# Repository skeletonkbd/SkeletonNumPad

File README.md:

# SkeletonNumPad

シンプルなNumpadです。現在、販売開始の準備中。

## 特徴
- アクリル積層ケース
- バックライトLED
- ホットスワップ

# 組み立て例

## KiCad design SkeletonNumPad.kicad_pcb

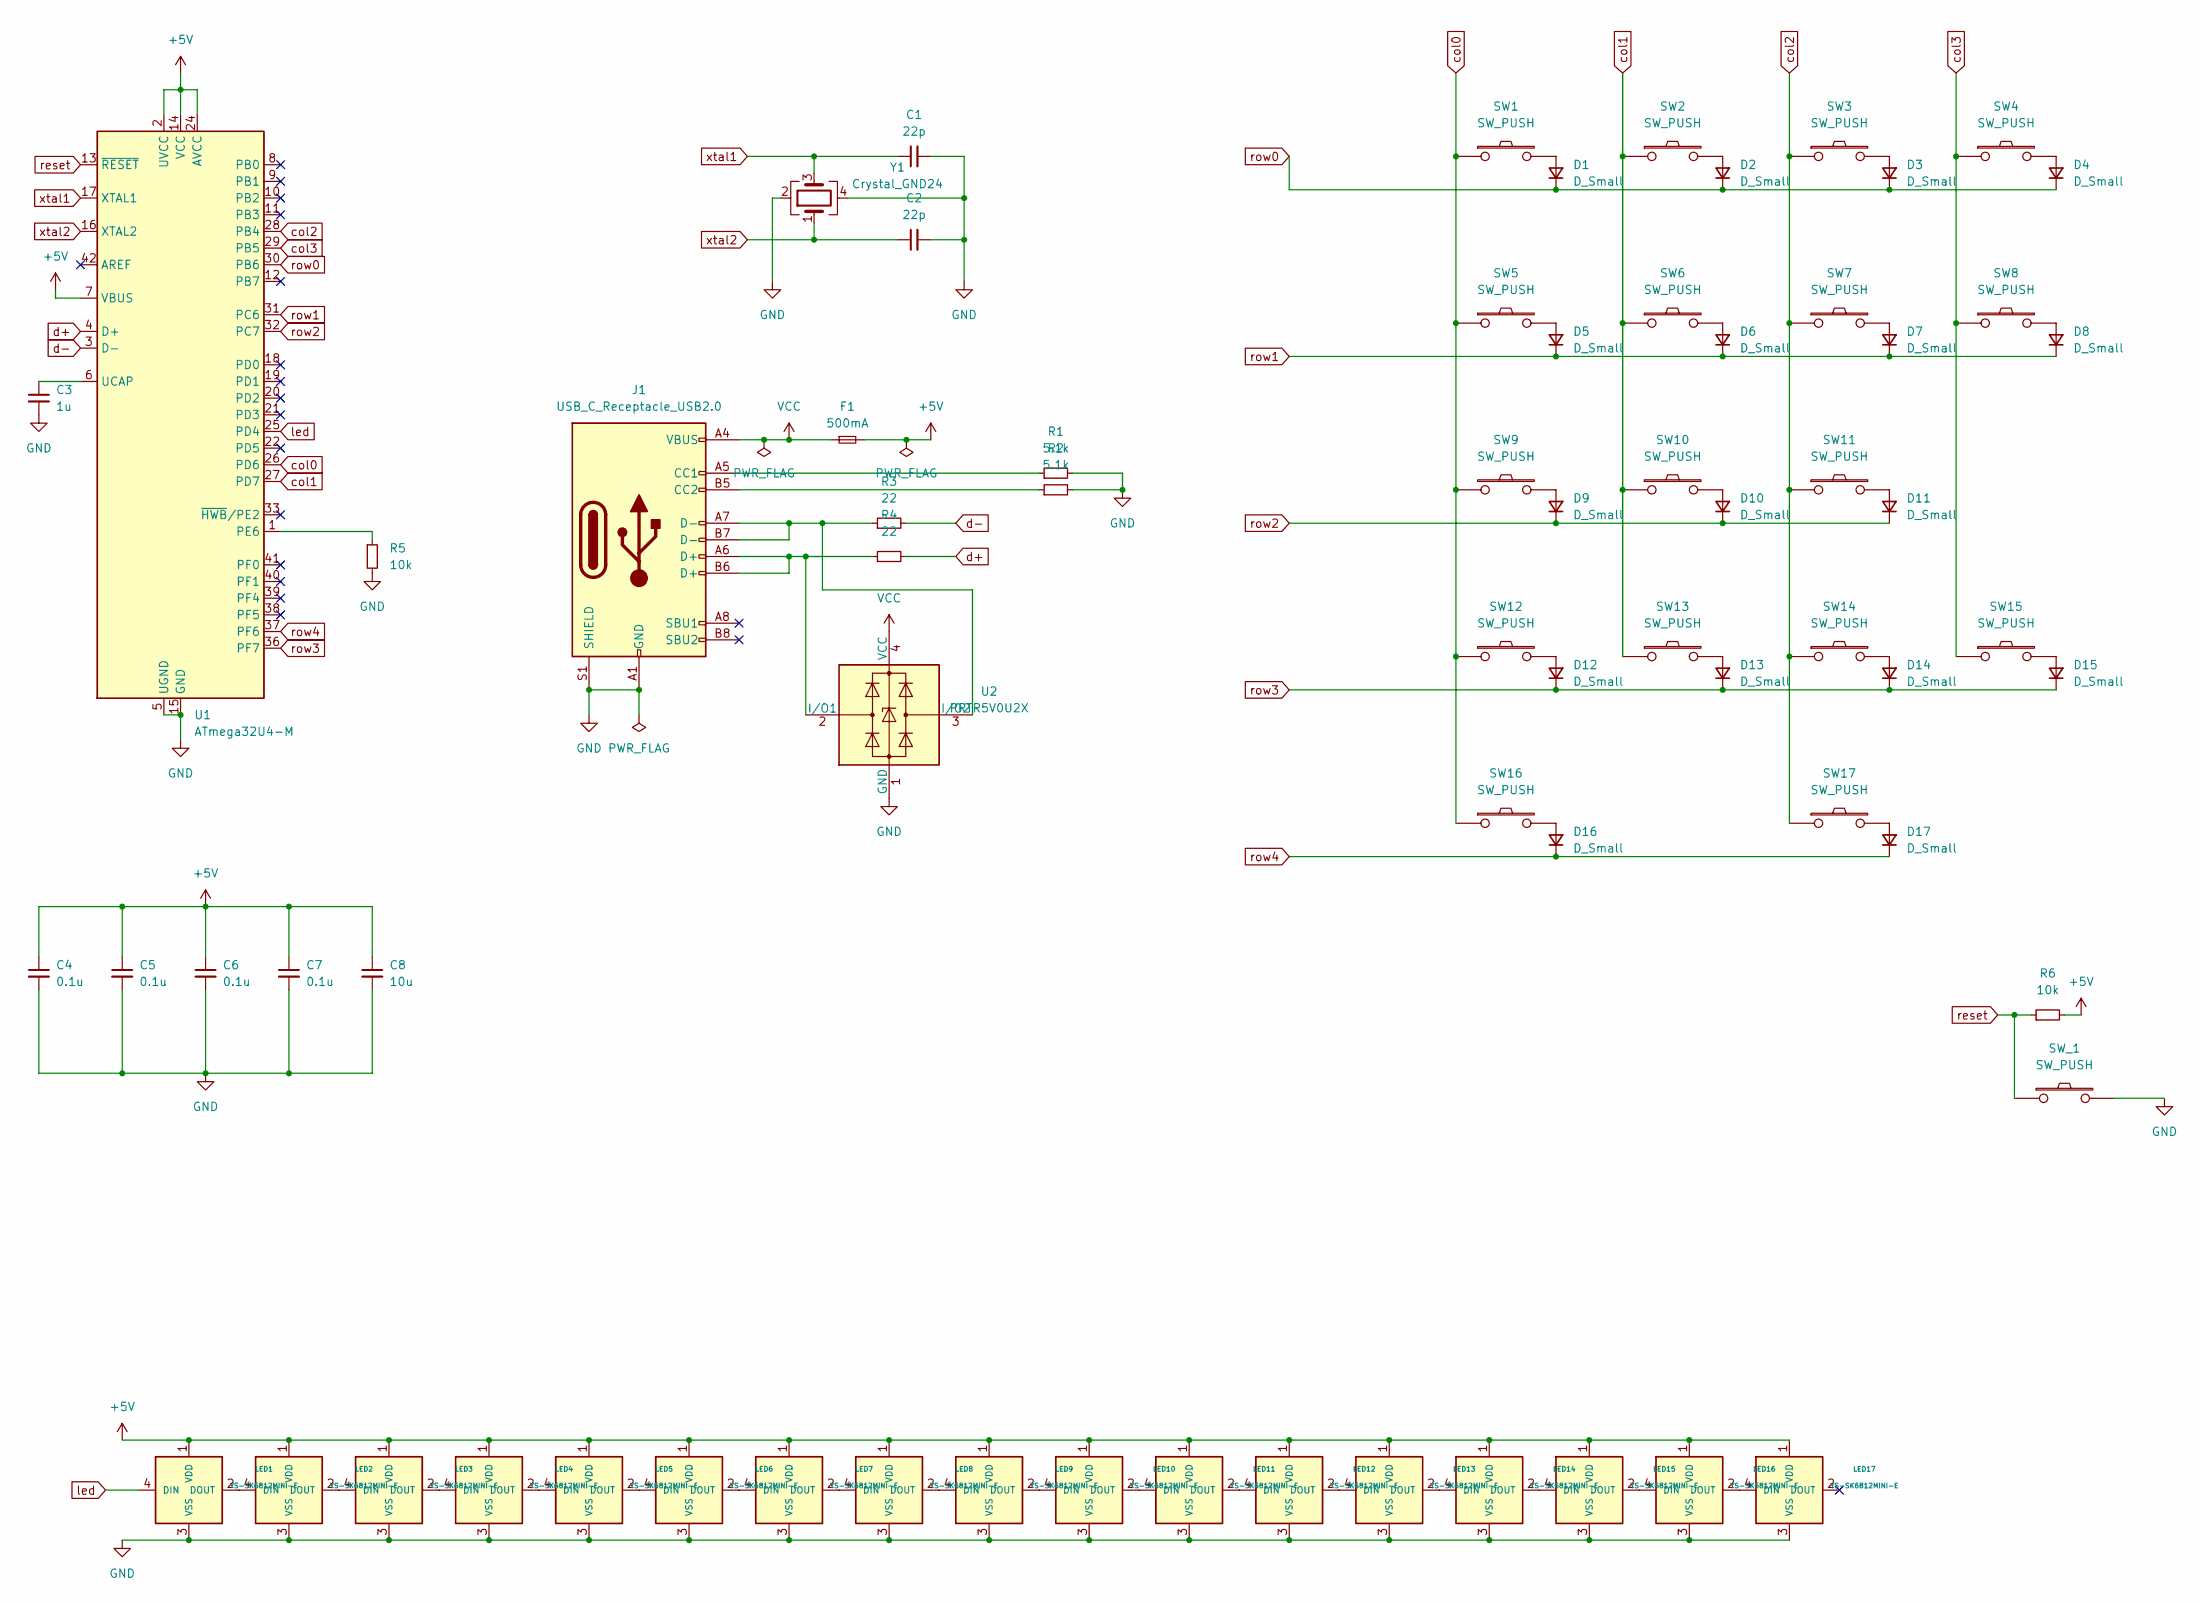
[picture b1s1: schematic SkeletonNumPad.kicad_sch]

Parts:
C1, C2: 22p; C_0805_2012Metric; LCSC C1804
C3: 1u; C_0805_2012Metric; LCSC C28323
C4, C5, C6, C7: 0.1u; C_0805_2012Metric; LCSC C49678
C8: 10u; C_0805_2012Metric; LCSC C15850
D1, D2, D3, D4, D5, D6, D7, D8, D9, D10, D11, D12, D13, D14, D15, D16, D17: D_Small; D_SOD-123; LCSC C81598
F1: 500mA; Fuse_1206_3216Metric; LCSC C70069
J1: USB_C_Receptacle_USB2.0; USB_C_Receptacle_Palconn_UTC16-G; LCSC C167321
LED1, LED2, LED3, LED4, LED5, LED6, LED7, LED8, LED9, LED10, LED11, LED12, LED13, LED14, LED15, LED16, LED17: YS-SK6812MINI-E
R1, R2: 5.1k; R_0805_2012Metric; LCSC C27834
R3, R4: 22; R_0805_2012Metric; LCSC C17561
R5, R6: 10k; R_0805_2012Metric; LCSC C17414
SW1, SW2, SW3, SW4, SW5, SW6, SW7, SW9, SW10, SW11, SW12, SW13, SW14, SW17: SW_PUSH; MXOnly-1U-Hotswap; LCSC C2803348
SW8, SW15: SW_PUSH; MXOnly-2U-Hotswap-VerticalStabilizers; LCSC C2803348
SW16: SW_PUSH; MXOnly-2U-Hotswap; LCSC C2803348
SW_1: SW_PUSH; SW_SPST_SKQG_WithStem; LCSC C455263
U1: ATmega32U4-M; QFN-44-1EP_7x7mm_P0.5mm_EP5.2x5.2mm; LCSC C112161
U2: PRTR5V0U2X; SOT-143; LCSC C2827688
Y1: Crystal_GND24; Crystal_SMD_3225-4Pin_3.2x2.5mm; LCSC C13738

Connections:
+5V: C4.1, C5.1, C6.1, C7.1, C8.1, F1.2, LED1.1 (VDD), LED2.1 (VDD), LED3.1 (VDD), LED4.1 (VDD), LED5.1 (VDD), LED6.1 (VDD), LED7.1 (VDD), LED8.1 (VDD), LED9.1 (VDD), LED10.1 (VDD), LED11.1 (VDD), LED12.1 (VDD), LED13.1 (VDD), LED14.1 (VDD), LED15.1 (VDD), LED16.1 (VDD), LED17.1 (VDD), R6.2, U1.2 (UVCC), U1.7 (VBUS), U1.14 (VCC), U1.24 (AVCC), U1.34 (VCC), U1.44 (AVCC)
GND: C1.2, C2.2, C3.2, C4.2, C5.2, C6.2, C7.2, C8.2, J1.A1 (GND), J1.A12 (GND), J1.B1 (GND), J1.B12 (GND), J1.S1 (SHIELD), LED1.3 (VSS), LED2.3 (VSS), LED3.3 (VSS), LED4.3 (VSS), LED5.3 (VSS), LED6.3 (VSS), LED7.3 (VSS), LED8.3 (VSS), LED9.3 (VSS), LED10.3 (VSS), LED11.3 (VSS), LED12.3 (VSS), LED13.3 (VSS), LED14.3 (VSS), LED15.3 (VSS), LED16.3 (VSS), LED17.3 (VSS), R1.2, R2.2, R5.2, SW_1.2, U1.5 (UGND), U1.15 (GND), U1.23 (GND), U1.35 (GND), U1.43 (GND), U1.45 (GND), U2.1 (GND), Y1.2, Y1.4
unnamed: C3.1, U1.6 (UCAP)
unnamed: D1.2 (A), SW1.2
unnamed: D2.2 (A), SW2.2
unnamed: D3.2 (A), SW3.2
unnamed: D4.2 (A), SW4.2
unnamed: D5.2 (A), SW5.2
unnamed: D6.2 (A), SW6.2
unnamed: D7.2 (A), SW7.2
unnamed: D8.2 (A), SW8.2
unnamed: D9.2 (A), SW9.2
unnamed: D10.2 (A), SW10.2
unnamed: D11.2 (A), SW11.2
unnamed: D12.2 (A), SW12.2
unnamed: D13.2 (A), SW13.2
unnamed: D14.2 (A), SW14.2
unnamed: D15.2 (A), SW15.2
unnamed: D16.2 (A), SW16.2
unnamed: D17.2 (A), SW17.2
unnamed: J1.A5 (CC1), R1.1
unnamed: J1.A6 (D+), J1.B6 (D+), R4.1, U2.2 (I/O1)
unnamed: J1.A7 (D-), J1.B7 (D-), R3.1, U2.3 (I/O2)
unnamed: J1.B5 (CC2), R2.1
unnamed: LED1.2 (DOUT), LED2.4 (DIN)
unnamed: LED2.2 (DOUT), LED3.4 (DIN)
unnamed: LED3.2 (DOUT), LED4.4 (DIN)
unnamed: LED4.2 (DOUT), LED5.4 (DIN)
unnamed: LED5.2 (DOUT), LED6.4 (DIN)
unnamed: LED6.2 (DOUT), LED7.4 (DIN)
unnamed: LED7.2 (DOUT), LED8.4 (DIN)
unnamed: LED8.2 (DOUT), LED9.4 (DIN)
unnamed: LED10.2 (DOUT), LED11.4 (DIN)
unnamed: LED9.2 (DOUT), LED10.4 (DIN)
unnamed: LED11.2 (DOUT), LED12.4 (DIN)
unnamed: LED12.2 (DOUT), LED13.4 (DIN)
unnamed: LED13.2 (DOUT), LED14.4 (DIN)
unnamed: LED14.2 (DOUT), LED15.4 (DIN)
unnamed: LED15.2 (DOUT), LED16.4 (DIN)
unnamed: LED16.2 (DOUT), LED17.4 (DIN)
unnamed: R5.1, U1.1 (PE6)
VCC: F1.1, J1.A4 (VBUS), J1.A9 (VBUS), J1.B4 (VBUS), J1.B9 (VBUS), U2.4 (VCC)
col0: SW1.1, SW5.1, SW9.1, SW12.1, SW16.1, U1.26 (PD6)
col1: SW2.1, SW6.1, SW10.1, SW13.1, U1.27 (PD7)
col2: SW3.1, SW7.1, SW11.1, SW14.1, SW17.1, U1.28 (PB4)
col3: SW4.1, SW8.1, SW15.1, U1.29 (PB5)
d+: R4.2, U1.4 (D+)
d-: R3.2, U1.3 (D-)
led: LED1.4 (DIN), U1.25 (PD4)
reset: R6.1, SW_1.1, U1.13 (~RESET)
row0: D1.1 (K), D2.1 (K), D3.1 (K), D4.1 (K), U1.30 (PB6)
row1: D5.1 (K), D6.1 (K), D7.1 (K), D8.1 (K), U1.31 (PC6)
row2: D9.1 (K), D10.1 (K), D11.1 (K), U1.32 (PC7)
row3: D12.1 (K), D13.1 (K), D14.1 (K), D15.1 (K), U1.36 (PF7)
row4: D16.1 (K), D17.1 (K), U1.37 (PF6)
xtal1: C1.1, U1.17 (XTAL1), Y1.3
xtal2: C2.1, U1.16 (XTAL2), Y1.1

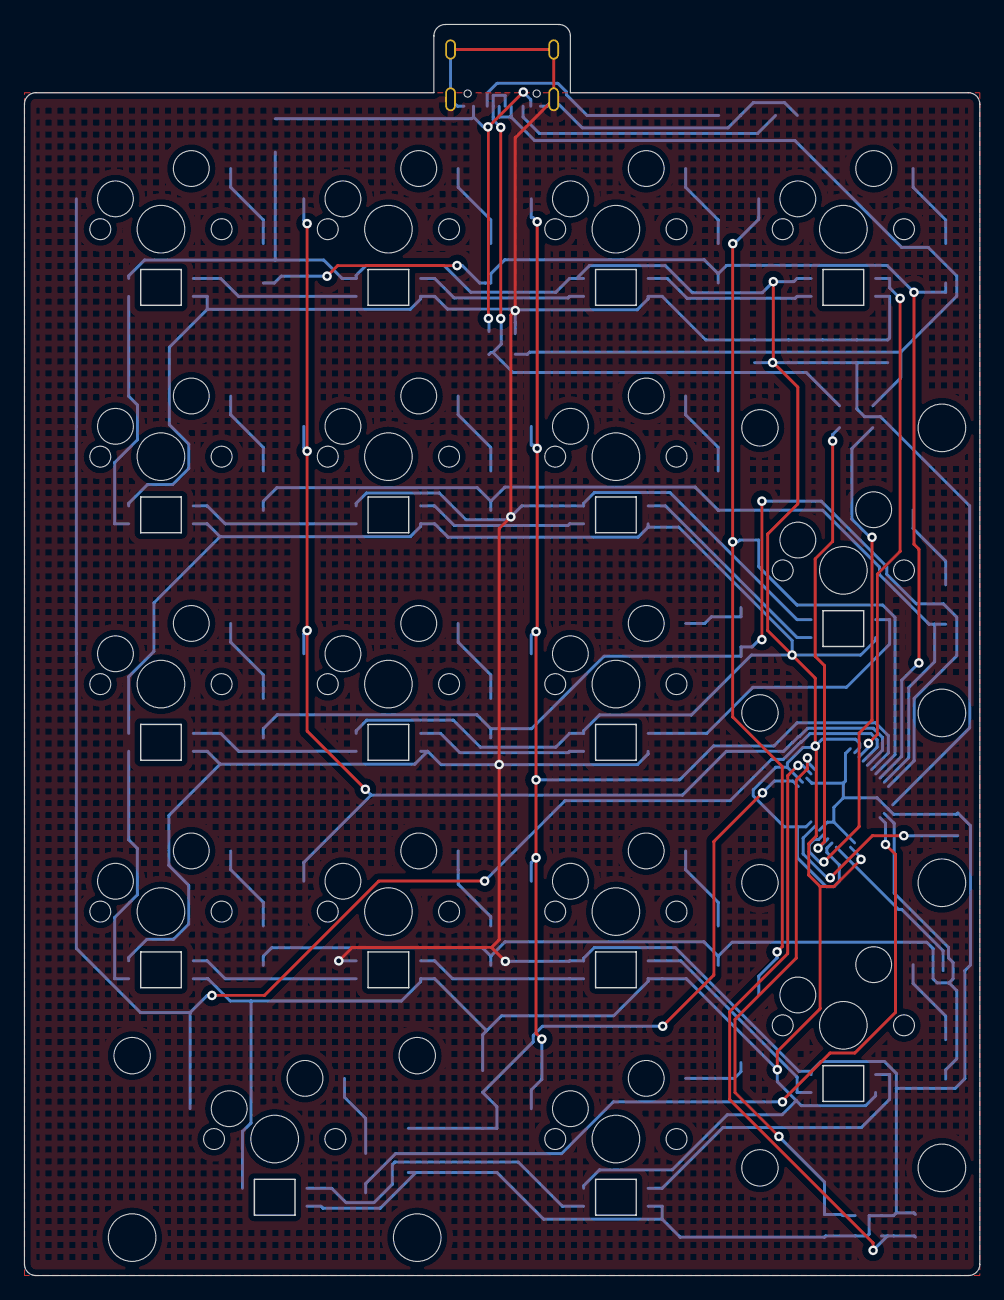
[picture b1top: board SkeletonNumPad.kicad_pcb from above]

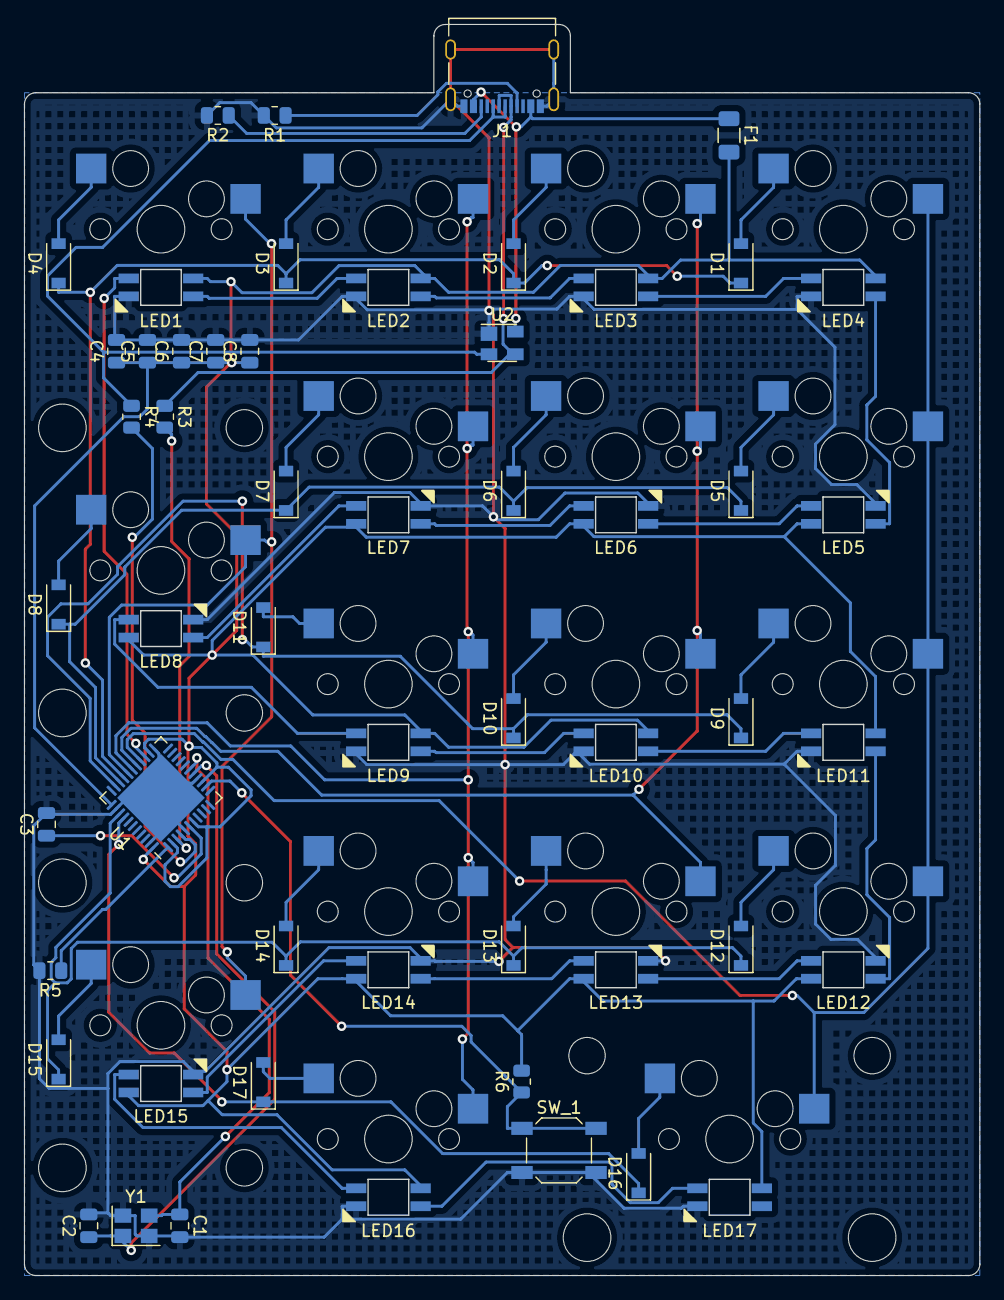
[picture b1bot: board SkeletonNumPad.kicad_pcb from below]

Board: 2 copper layers, 80.0 x 104.8 mm, 71 parts (71 on the bottom side), 57 nets.

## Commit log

2022-01-16 add library
2022-01-18 Customize footprints
2022-02-21 with WS2812B-2020
2022-02-21 with SK6812mini-e
2022-03-13 rev1
2022-03-13 readme
2022-03-19 case v2
2023-09-14 add firmware
